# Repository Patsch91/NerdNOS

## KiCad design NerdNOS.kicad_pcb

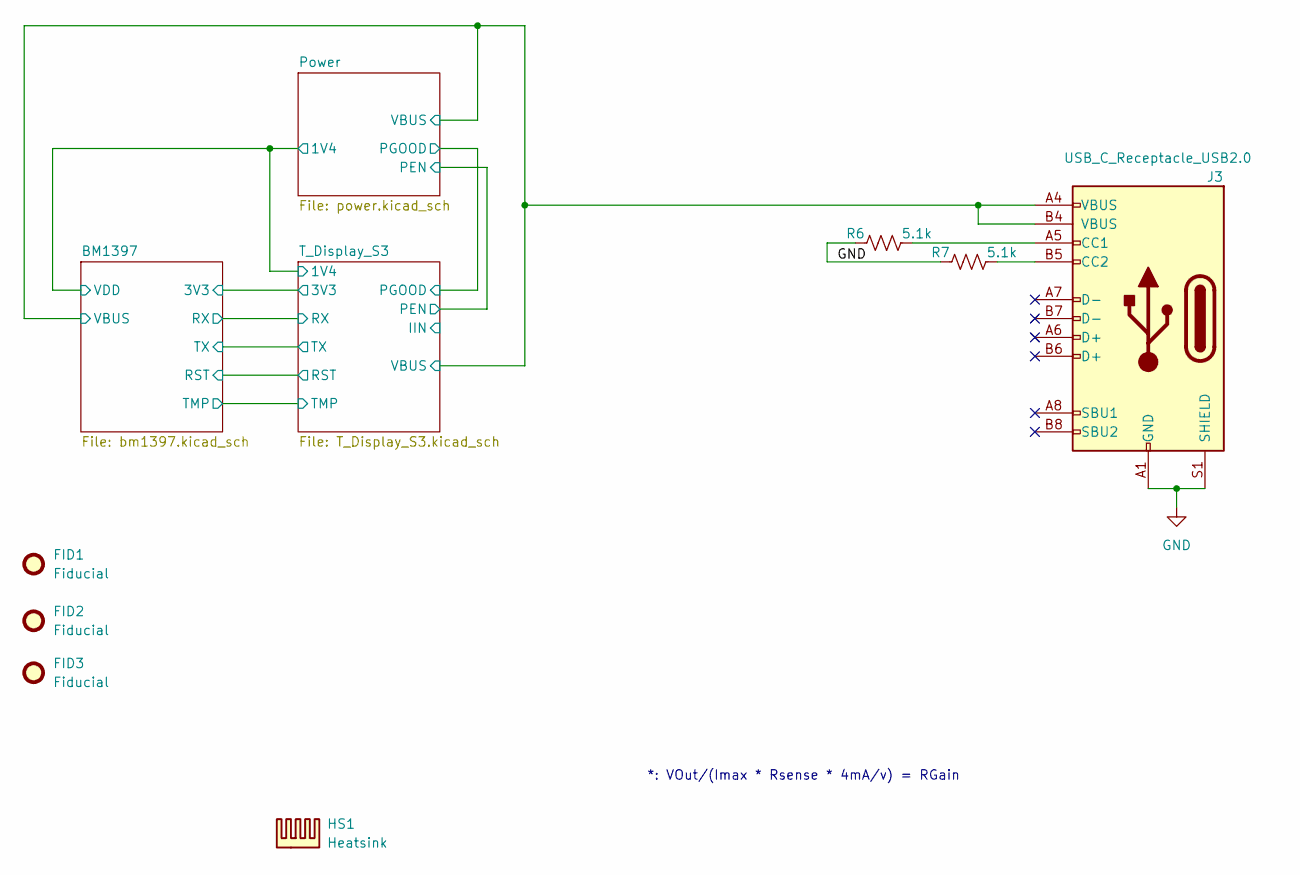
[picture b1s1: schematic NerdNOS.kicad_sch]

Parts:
FID1, FID2, FID3: Fiducial; Fiducial_1mm_Mask2mm
HS1: Heatsink; 960-19-15-F-AB-0
J3: USB_C_Receptacle_USB2.0; USB_C_Receptacle_GCT_USB4105-xx-A_16P_TopMnt_Horizontal; PARTNO USB4105-GF-A
R6, R7: 5.1k; R_0402_1005Metric; PARTNO RMCF0402JT5K10

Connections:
/Power/VBUS: J3.A4 (VBUS), J3.B4 (VBUS); also elsewhere on the board
GND: J3.A1 (GND), J3.B1 (GND), J3.S1 (SHIELD), R6.1, R7.1; also elsewhere on the board
unnamed: J3.A5 (CC1), R6.2
unnamed: J3.B5 (CC2), R7.2

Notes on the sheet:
*: VOut/(Imax * Rsense * 4mA/v) = RGain

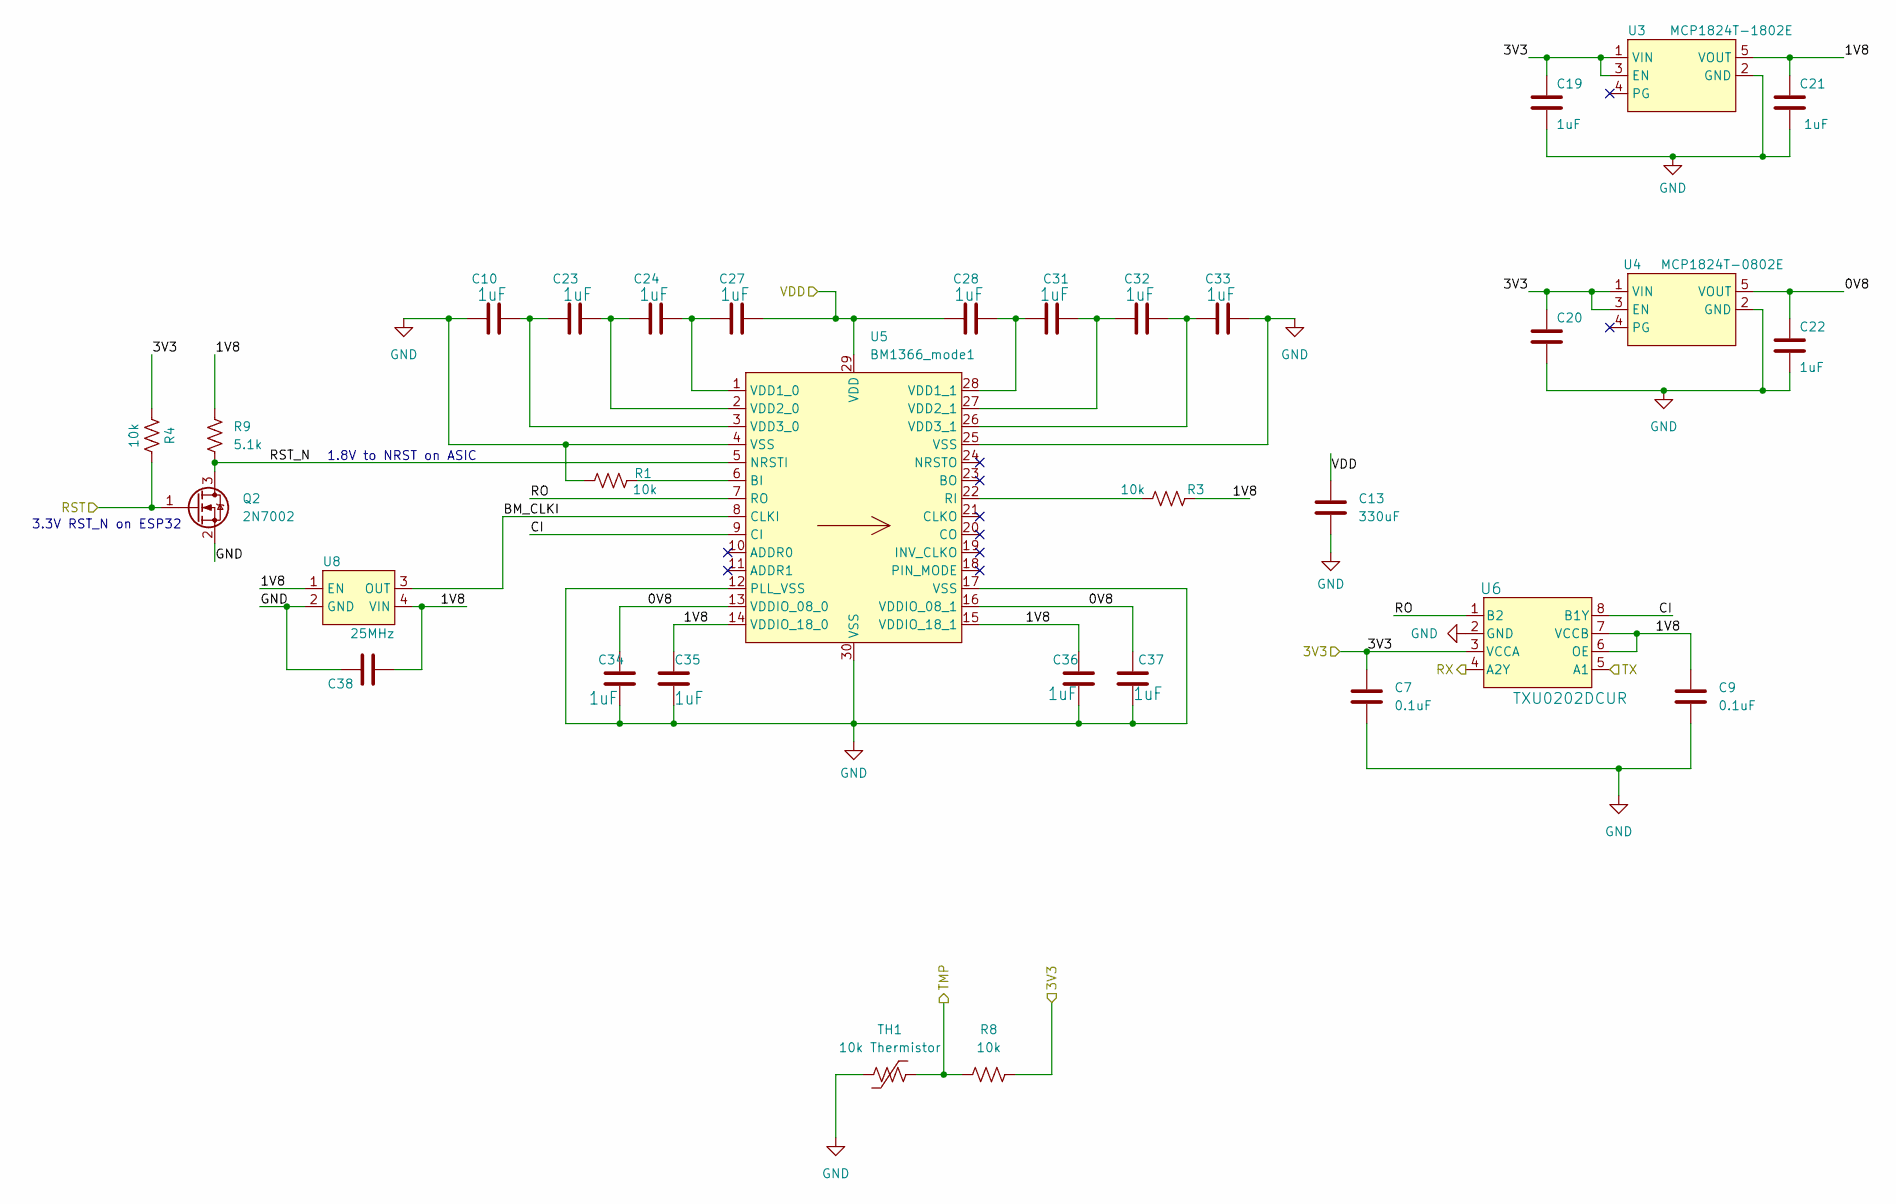
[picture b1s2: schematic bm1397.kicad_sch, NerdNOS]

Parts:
C7, C9, C20, C38: 0.1uF; C_0402_1005Metric; PARTNO KGM05AR71C104KH
C10, C19, C21, C22, C23, C24, C27, C28, C31, C32, C33, C34, C35, C36, C37: 1uF; C_0402_1005Metric; PARTNO EMK105BJ105MV-F
C13: 330uF; C_1210_3225Metric; PARTNO GRM32ER60G337ME05K
Q2: 2N7002; SOT-23; PARTNO 2N7002
R1: 10k; R_0402_1005Metric
R3, R4, R8: 10k; R_0402_1005Metric; PARTNO RC0402JR-0710KL
R9: 5.1k; R_0402_1005Metric; PARTNO ERJ-2RKF2491X
TH1: 10k Thermistor; R_0402_1005Metric; PARTNO NTCG103JF103FT1
U3: MCP1824T-1802E; SOT-23-5; PARTNO MCP1824T-1802E/OT
U4: MCP1824T-0802E; SOT-23-5; PARTNO MCP1824T-0802E/OT
U5: BM1366_mode1; BM1366
U6: TXU0202DCUR; SO8_DCU_TEX; PARTNO TXU0202DCUR
U8: 25MHz; O 25,0-JO32-B-1V3-1-T1-LF; PARTNO O 25,0-JO32-B-1V3-1-T1-LF

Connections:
/BM1397/0V8: C22.1, C34.1, C37.1, U4.5 (VOUT), U5.13 (VDDIO_08_0), U5.16 (VDDIO_08_1)
/BM1397/1V8: C9.1, C21.1, C35.1, C36.1, C38.2, R3.2, R9.2, U3.5 (VOUT), U5.14 (VDDIO_18_0), U5.15 (VDDIO_18_1), U6.6 (OE), U6.7 (VCCB), U8.1 (EN), U8.4 (VIN)
/BM1397/3V3: C7.2, C19.1, C20.1, R4.1, R8.2, U3.1 (VIN), U3.3 (EN), U4.1 (VIN), U4.3 (EN), U6.3 (VCCA); also elsewhere on the board
/BM1397/BM_CLKI: U5.8 (CLKI), U8.3 (OUT)
/BM1397/CI: U5.9 (CI), U6.8 (B1Y)
/BM1397/RO: U5.7 (RO), U6.1 (B2)
/BM1397/RST: Q2.1 (G), R4.2; also elsewhere on the board
/BM1397/RST_N: Q2.3 (D), R9.1, U5.5 (NRSTI)
/BM1397/RX: U6.4 (A2Y); also elsewhere on the board
/BM1397/TMP: R8.1, TH1.2; also elsewhere on the board
/BM1397/TX: U6.5 (A1); also elsewhere on the board
/BM1397/VDD: C13.1, C27.2, C28.1, U5.29 (VDD); also elsewhere on the board
GND: C7.1, C9.2, C10.1, C13.2, C19.2, C20.2, C21.2, C22.2, C33.2, C34.2, C35.2, C36.2, C37.2, C38.1, Q2.2 (S), R1.1, TH1.1, U3.2 (GND), U4.2 (GND), U5.4 (VSS), U5.12 (PLL_VSS), U5.17 (VSS), U5.25 (VSS), U5.30 (VSS), U6.2 (GND), U8.2 (GND); also elsewhere on the board
unnamed: R1.2, U5.6 (BI)
unnamed: R3.1, U5.22 (RI)
unnamed: C24.2, C27.1, U5.1 (VDD1_0)
unnamed: C28.2, C31.1, U5.28 (VDD1_1)
unnamed: C23.2, C24.1, U5.2 (VDD2_0)
unnamed: C31.2, C32.1, U5.27 (VDD2_1)
unnamed: C10.2, C23.1, U5.3 (VDD3_0)
unnamed: C32.2, C33.1, U5.26 (VDD3_1)

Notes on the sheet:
1.8V to NRST on ASIC
3.3V RST_N on ESP32

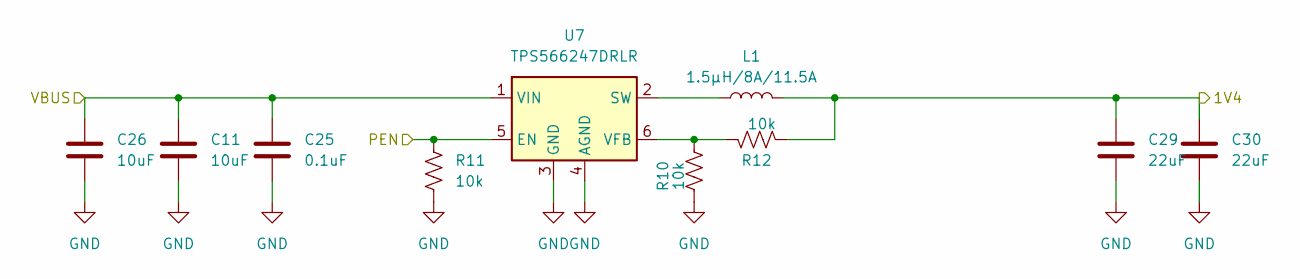
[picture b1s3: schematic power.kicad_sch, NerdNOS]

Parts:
C11, C26: 10uF; C_0805_2012Metric; PARTNO C0805C106K8PACTU
C25: 0.1uF; C_0402_1005Metric; PARTNO KGM05AR71C104KH
C29, C30: 22uF; C_0805_2012Metric; PARTNO GRM21BR60J226ME39L
L1: 1.5µH/8A/11.5A; L_Cenker_CKCS8040
R10, R12: 10k; R_0402_1005Metric; PARTNO RC0603FR-0740K2L
R11: 10k; R_0402_1005Metric; PARTNO RC0402JR-0710KL
U7: TPS566247DRLR; SOT-563

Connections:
/BM1397/VDD: C29.1, C30.1, L1.2, R12.2; also elsewhere on the board
/Power/PEN: R11.1, U7.5 (EN); also elsewhere on the board
/Power/VBUS: C11.1, C25.1, C26.1, U7.1 (VIN); also elsewhere on the board
GND: C11.2, C25.2, C26.2, C29.2, C30.2, R10.1, R11.2, U7.3 (GND), U7.4 (AGND); also elsewhere on the board
unnamed: L1.1, U7.2 (SW)
unnamed: R10.2, R12.1, U7.6 (VFB)

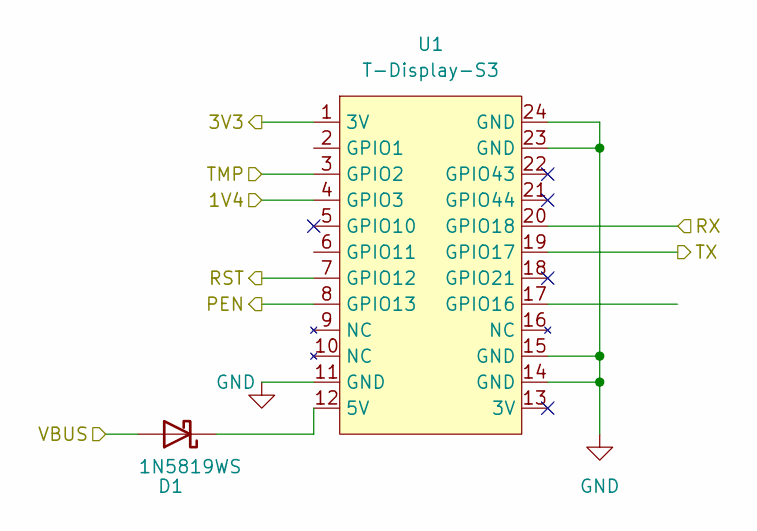
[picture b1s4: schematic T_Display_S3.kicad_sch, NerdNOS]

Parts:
D1: 1N5819WS; D_SOD-123
U1: T-Display-S3; T-Display-S3-friction-fit

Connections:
/BM1397/3V3: U1.1 (3V); also elsewhere on the board
/BM1397/RST: U1.7 (GPIO12); also elsewhere on the board
/BM1397/RX: U1.20 (GPIO18); also elsewhere on the board
/BM1397/TMP: U1.3 (GPIO2); also elsewhere on the board
/BM1397/TX: U1.19 (GPIO17); also elsewhere on the board
/BM1397/VDD: U1.4 (GPIO3); also elsewhere on the board
/Power/PEN: U1.8 (GPIO13); also elsewhere on the board
/Power/VBUS: D1.2 (A); also elsewhere on the board
GND: U1.11 (GND), U1.14 (GND), U1.15 (GND), U1.23 (GND), U1.24 (GND); also elsewhere on the board
unnamed: D1.1 (K), U1.12 (5V)

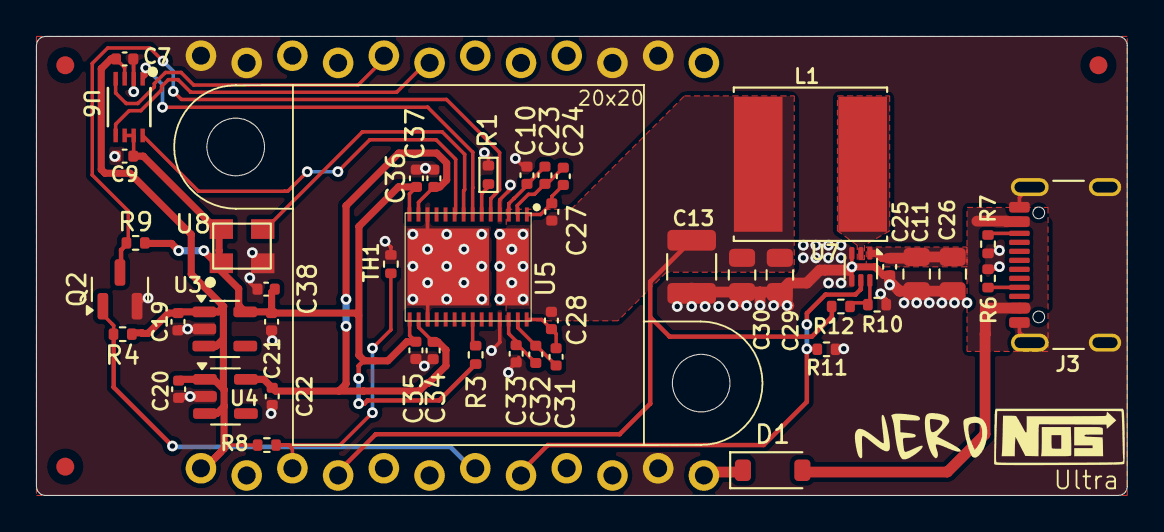
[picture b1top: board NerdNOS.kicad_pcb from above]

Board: 2 copper layers, 60.6 x 25.5 mm, 51 parts (1 on the bottom side), 28 nets.

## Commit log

2024-09-18 BM1366
    BM1366 tryout
2024-10-14 Create LICENSE
